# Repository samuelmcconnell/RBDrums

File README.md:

# RBDrums
Hardware for creating Rock Band and Guitar Hero compatible drumsets

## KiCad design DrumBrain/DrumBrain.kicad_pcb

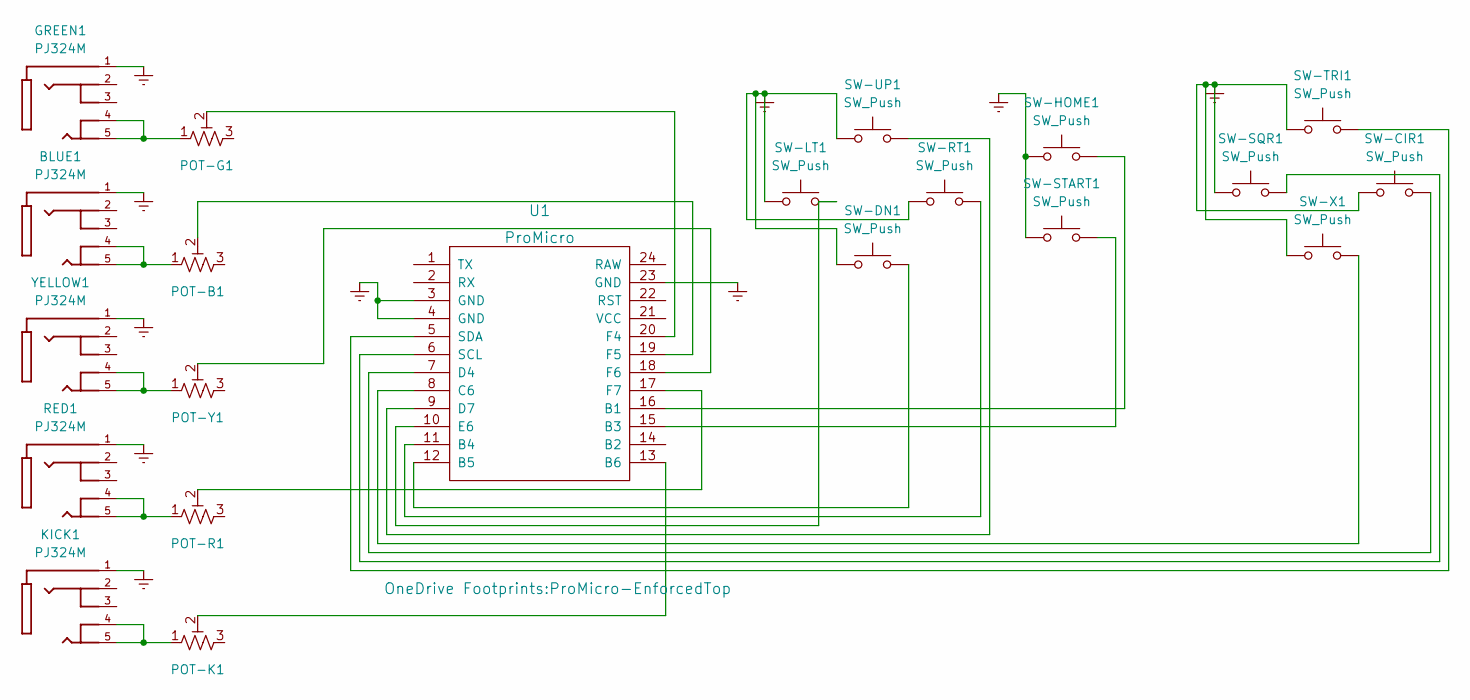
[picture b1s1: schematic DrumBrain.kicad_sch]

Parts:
BLUE1: PJ324M; WENZHOU_PJ324M; PARTREV N/A
GREEN1: PJ324M; WENZHOU_PJ324M; PARTREV N/A
KICK1: PJ324M; WENZHOU_PJ324M; PARTREV N/A
POT-B1: R_Potentiometer_Trim_US; Potentiometer_Bourns_3296W_Vertical
POT-G1: R_Potentiometer_Trim_US; Potentiometer_Bourns_3296W_Vertical
POT-K1: R_Potentiometer_Trim_US; Potentiometer_Bourns_3296W_Vertical
POT-R1: R_Potentiometer_Trim_US; Potentiometer_Bourns_3296W_Vertical
POT-Y1: R_Potentiometer_Trim_US; Potentiometer_Bourns_3296W_Vertical
RED1: PJ324M; WENZHOU_PJ324M; PARTREV N/A
SW-CIR1: SW_Push; SW_Cherry_MX_PCB_1.00u
SW-DN1: SW_Push; SW_Cherry_MX_PCB_1.00u
SW-HOME1: SW_Push; SW_Cherry_MX_PCB_1.00u
SW-LT1: SW_Push; SW_Cherry_MX_PCB_1.00u
SW-RT1: SW_Push; SW_Cherry_MX_PCB_1.00u
SW-SQR1: SW_Push; SW_Cherry_MX_PCB_1.00u
SW-START1: SW_Push; SW_Cherry_MX_PCB_1.00u
SW-TRI1: SW_Push; SW_Cherry_MX_PCB_1.00u
SW-UP1: SW_Push; SW_Cherry_MX_PCB_1.00u
SW-X1: SW_Push; SW_Cherry_MX_PCB_1.00u
U1: ProMicro; ProMicro-EnforcedTop
YELLOW1: PJ324M; WENZHOU_PJ324M; PARTREV N/A

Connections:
Earth: BLUE1.1, GREEN1.1, KICK1.1, RED1.1, SW-CIR1.1, SW-DN1.1, SW-HOME1.1, SW-LT1.1, SW-RT1.1, SW-SQR1.1, SW-START1.1, SW-TRI1.1, SW-UP1.1, SW-X1.1, U1.3 (GND), U1.4 (GND), U1.23 (GND), YELLOW1.1
unnamed: BLUE1.4, BLUE1.5, POT-B1.1
unnamed: GREEN1.4, GREEN1.5, POT-G1.1
unnamed: KICK1.4, KICK1.5, POT-K1.1
unnamed: POT-B1.2, U1.19 (F5)
unnamed: POT-G1.2, U1.20 (F4)
unnamed: POT-K1.2, U1.13 (B6)
unnamed: POT-R1.2, U1.17 (F7)
unnamed: POT-Y1.2, U1.18 (F6)
unnamed: POT-R1.1, RED1.4, RED1.5
unnamed: SW-CIR1.2, U1.7 (D4)
unnamed: SW-DN1.2, U1.12 (B5)
unnamed: SW-HOME1.2, U1.16 (B1)
unnamed: SW-LT1.2, U1.10 (E6)
unnamed: SW-RT1.2, U1.11 (B4)
unnamed: SW-SQR1.2, U1.6 (SCL)
unnamed: SW-START1.2, U1.15 (B3)
unnamed: SW-TRI1.2, U1.5 (SDA)
unnamed: SW-UP1.2, U1.9 (D7)
unnamed: SW-X1.2, U1.8 (C6)
unnamed: POT-Y1.1, YELLOW1.4, YELLOW1.5

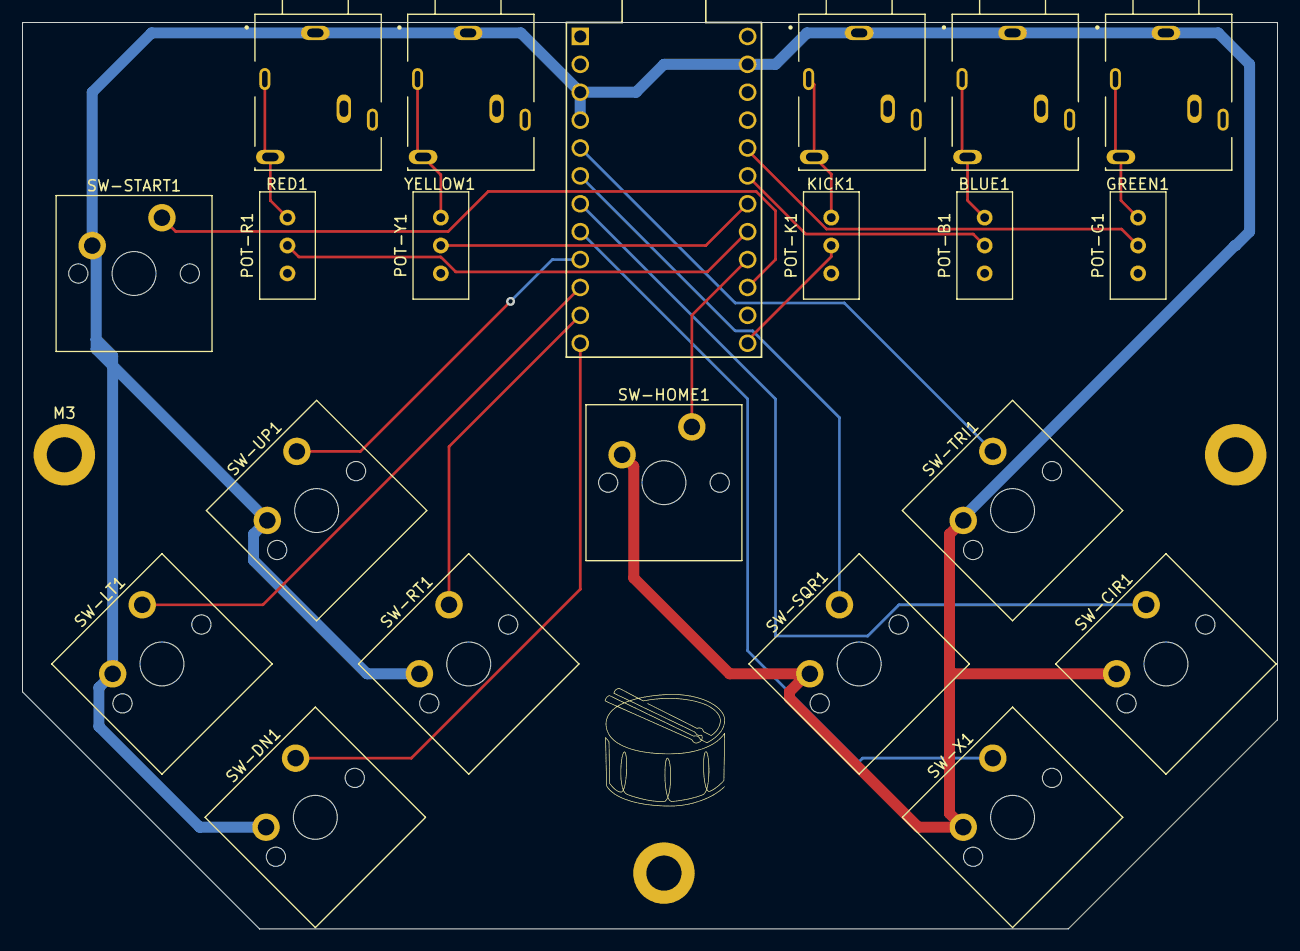
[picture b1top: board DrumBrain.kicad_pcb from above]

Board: 2 copper layers, 114.3 x 82.6 mm, 22 parts (0 on the bottom side), 21 nets.

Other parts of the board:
M3: MountingHole_3.2mm_M3_DIN965_Pad

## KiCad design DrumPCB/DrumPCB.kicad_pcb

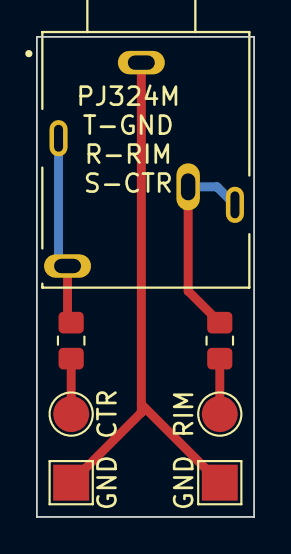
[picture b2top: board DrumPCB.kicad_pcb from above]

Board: 2 copper layers, 12.1 x 26.7 mm, 7 parts (0 on the bottom side), 5 nets.

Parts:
CTR: TestPoint; TestPoint_Pad_D2.0mm
GND: TestPoint; TestPoint_Pad_2.0x2.0mm
GND#2: TestPoint; TestPoint_Pad_2.0x2.0mm
J2: PJ324M; WENZHOU_PJ324M
R1, R2: R_US; R_0805_2012Metric_Pad1.20x1.40mm_HandSolder
RIM: TestPoint; TestPoint_Pad_D2.0mm

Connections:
Earth: GND.1, GND#2.1, J2.1
unnamed: J2.4, J2.5, R1.1
unnamed: CTR.1, R1.2
unnamed: J2.2, J2.3, R2.1
unnamed: R2.2, RIM.1
